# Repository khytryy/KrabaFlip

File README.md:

# KrabaFlip

## My DIY console based on RPI CM5

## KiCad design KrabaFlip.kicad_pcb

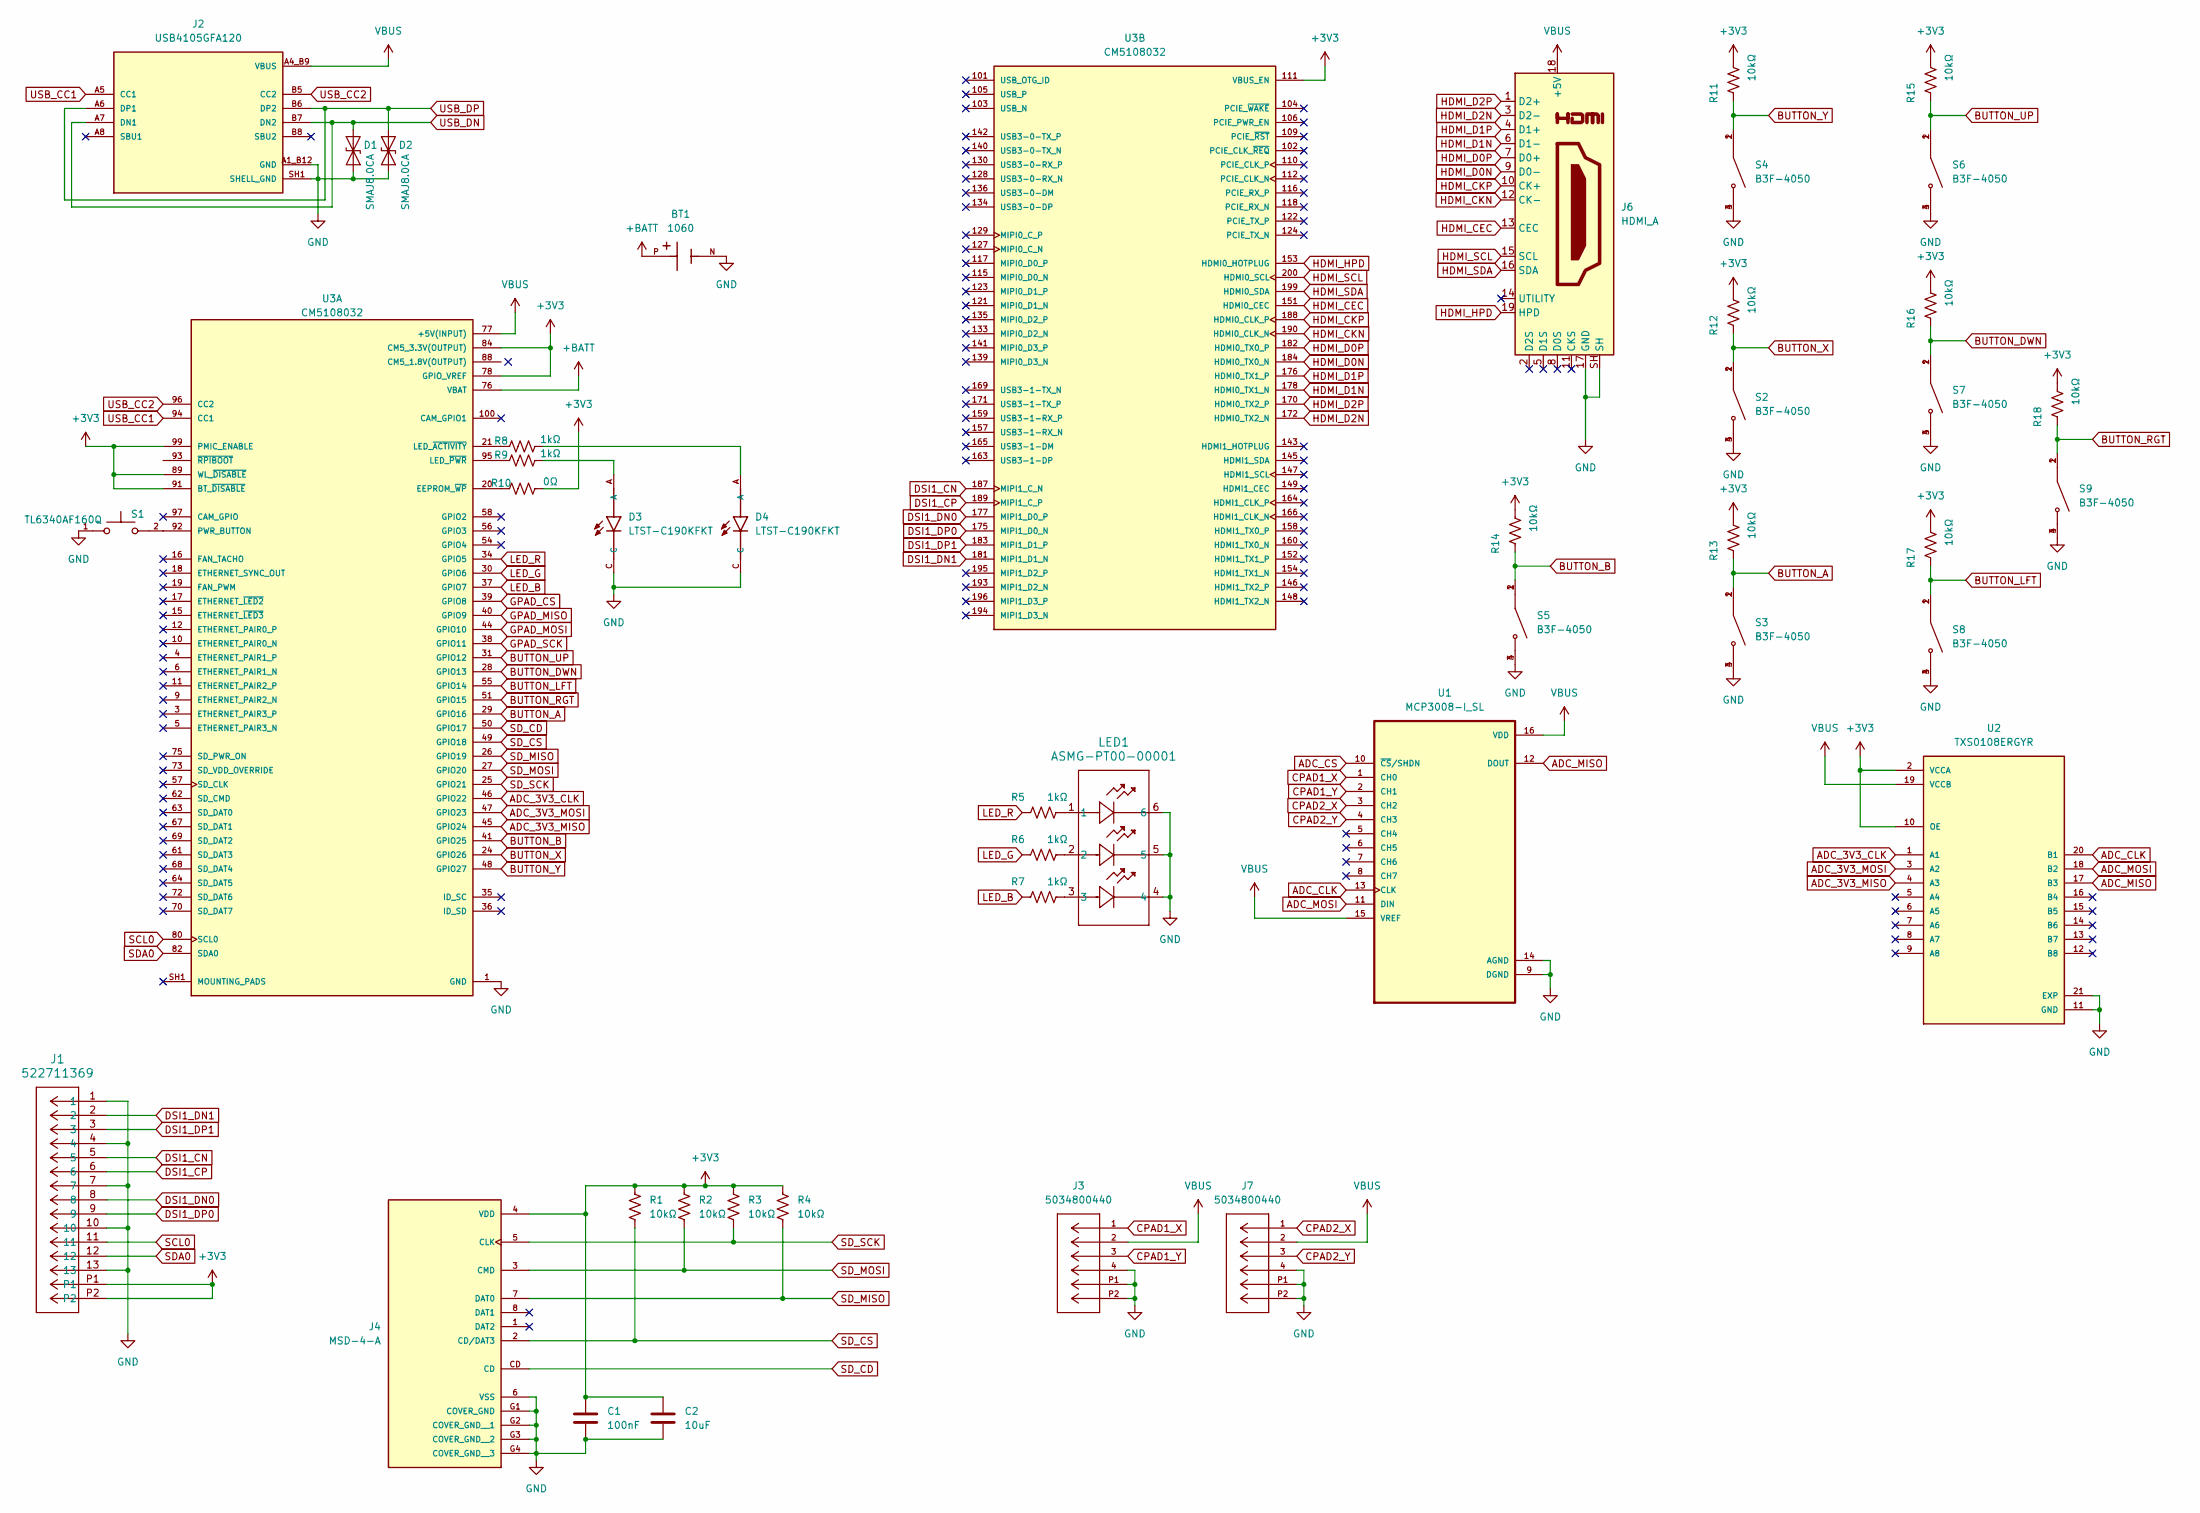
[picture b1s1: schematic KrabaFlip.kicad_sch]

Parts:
BT1: 1060; BAT_1060; PARTREV L; DigiKey_Part_Number 36-1060-ND
C1: 100nF; C_0402_1005Metric
C2: 10uF; C_0402_1005Metric
D1, D2: SMAJ8.0CA; D_SMA
D3, D4: LTST-C190KFKT; LEDM1608X80; DigiKey_Part_Number 160-1434-1-ND
J1: 522711369; CON_522711369_MOL
J2: USB4105GFA120; GCT_USB4105GFA120; PARTREV B3; DigiKey_Part_Number 2073-USB4105-GF-A-120CT-ND
J3, J7: 5034800440; CON_5034800440_MOL; MANUFACTURER_PART_NUMBER 5034800440; DigiKey_Part_Number 900-5034800440CT-ND
J4: MSD-4-A; CUI_MSD-4-A; PARTREV 1.0
J6: HDMI_A; HDMI_A_Amphenol_10029449-x01xLF_Horizontal
LED1: ASMG-PT00-00001; ASMG-PT00_BRA
R1, R2, R3, R4, R11, R12, R13, R14, R15, R16, R17, R18: 10kΩ; R_0402_1005Metric
R5, R6, R7, R8, R9: 1kΩ; R_0402_1005Metric
R10: 0Ω; R_0402_1005Metric
S1: TL6340AF160Q; SW_TL6340AF160Q; PARTREV 10.23.2019; DigiKey_Part_Number 141-TL6340AF160QCT-ND
S2, S3, S4, S5, S6, S7, S8, S9: B3F-4050; SW_B3F-4050; Digi-Key_Part_Number SW414-ND
U1: MCP3008-I_SL; SOIC127P600X175-16N; DigiKey_Part_Number MCP3008-I/SL-ND
U2: TXS0108ERGYR; IC_TXS0108ERGYR; PARTREV H; DigiKey_Part_Number 296-24806-1-ND
U3: CM5108032; MODULE_CM5108032; PARTREV 2024-11-27

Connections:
+3V3: C1.1, C2.1, J1.P1, J1.P2, J4.4 (VDD), R1.1, R2.1, R3.1, R4.1, R10.2, R11.2, R12.2, R13.2, R14.2, R15.2, R16.2, R17.2, R18.2, U2.2 (VCCA), U2.10 (OE), U3.78 (GPIO_VREF), U3.84 (CM5_3.3V(OUTPUT)), U3.86 (CM5_3.3V(OUTPUT)), U3.89 (WL_~DISABLE), U3.91 (BT_~DISABLE), U3.99 (PMIC_ENABLE), U3.111 (VBUS_EN)
+BATT: BT1.P, U3.76 (VBAT)
ADC_3V3_CLK: U2.1 (A1), U3.46 (GPIO22)
ADC_3V3_MISO: U2.4 (A3), U3.45 (GPIO24)
ADC_3V3_MOSI: U2.3 (A2), U3.47 (GPIO23)
ADC_CLK: U1.13 (CLK), U2.20 (B1)
ADC_CS: U1.10 (~CS/SHDN)
ADC_MISO: U1.12 (DOUT), U2.17 (B3)
ADC_MOSI: U1.11 (DIN), U2.18 (B2)
BUTTON_A: R13.1, S3.1, S3.2, U3.29 (GPIO16)
BUTTON_B: R14.1, S5.1, S5.2, U3.41 (GPIO25)
BUTTON_DWN: R16.1, S7.1, S7.2, U3.28 (GPIO13)
BUTTON_LFT: R17.1, S8.1, S8.2, U3.55 (GPIO14)
BUTTON_RGT: R18.1, S9.1, S9.2, U3.51 (GPIO15)
BUTTON_UP: R15.1, S6.1, S6.2, U3.31 (GPIO12)
BUTTON_X: R12.1, S2.1, S2.2, U3.24 (GPIO26)
BUTTON_Y: R11.1, S4.1, S4.2, U3.48 (GPIO27)
CM5_1.8V(OUTPUT): U3.88 (CM5_1.8V(OUTPUT)), U3.90 (CM5_1.8V(OUTPUT))
CPAD1_X: J3.1, U1.1 (CH0)
CPAD1_Y: J3.3, U1.2 (CH1)
CPAD2_X: J7.1, U1.3 (CH2)
CPAD2_Y: J7.3, U1.4 (CH3)
DSI1_CN: J1.5, U3.187 (MIPI1_C_N)
DSI1_CP: J1.6, U3.189 (MIPI1_C_P)
DSI1_DN0: J1.8, U3.177 (MIPI1_D0_P)
DSI1_DN1: J1.2, U3.181 (MIPI1_D1_N)
DSI1_DP0: J1.9, U3.175 (MIPI1_D0_N)
DSI1_DP1: J1.3, U3.183 (MIPI1_D1_P)
GND: BT1.N, C1.2, C2.2, D1.1 (A1), D2.1 (A1), D3.C, D4.C, J1.1, J1.4, J1.7, J1.10, J1.13, J2.A1_B12 (GND), J2.B1_A12 (GND), J2.SH1 (SHELL_GND), J2.SH2 (SHELL_GND), J2.SH3 (SHELL_GND), J2.SH4 (SHELL_GND), J3.4, J3.P1, J3.P2, J4.6 (VSS), J4.G1 (COVER_GND), J4.G2 (COVER_GND__1), J4.G3 (COVER_GND__2), J4.G4 (COVER_GND__3), J6.17 (GND), J6.SH, J7.4, J7.P1, J7.P2, LED1.4, LED1.5, LED1.6, S1.1, S2.3, S2.4, S3.3, S3.4, S4.3, S4.4, S5.3, S5.4, S6.3, S6.4, S7.3, S7.4, S8.3, S8.4, S9.3, S9.4, U1.9 (DGND), U1.14 (AGND), U2.11 (GND), U2.21 (EXP), U3.1 (GND), U3.2 (GND), U3.7 (GND), U3.8 (GND), U3.13 (GND), U3.14 (GND), U3.22 (GND), U3.23 (GND), U3.32 (GND), U3.33 (GND), U3.42 (GND), U3.43 (GND), U3.52 (GND), U3.53 (GND), U3.59 (GND), U3.60 (GND), U3.65 (GND), U3.66 (GND), U3.71 (GND), U3.74 (GND), U3.98 (GND), U3.107 (GND), U3.108 (GND), U3.113 (GND), U3.114 (GND), U3.119 (GND), U3.120 (GND), U3.125 (GND), U3.126 (GND), U3.131 (GND), U3.132 (GND), U3.137 (GND), U3.138 (GND), U3.144 (GND), U3.150 (GND), U3.155 (GND), U3.156 (GND), U3.161 (GND), U3.162 (GND), U3.167 (GND), U3.168 (GND), U3.173 (GND), U3.174 (GND), U3.179 (GND), U3.180 (GND), U3.185 (GND), U3.186 (GND), U3.191 (GND), U3.192 (GND), U3.197 (GND), U3.198 (GND)
GPAD_CS: U3.39 (GPIO8)
GPAD_MISO: U3.40 (GPIO9)
GPAD_MOSI: U3.44 (GPIO10)
GPAD_SCK: U3.38 (GPIO11)
HDMI_CEC: J6.13 (CEC), U3.151 (HDMI0_CEC)
HDMI_CKN: J6.12 (CK-), U3.190 (HDMI0_CLK_N)
HDMI_CKP: J6.10 (CK+), U3.188 (HDMI0_CLK_P)
HDMI_D0N: J6.9 (D0-), U3.184 (HDMI0_TX0_N)
HDMI_D0P: J6.7 (D0+), U3.182 (HDMI0_TX0_P)
HDMI_D1N: J6.6 (D1-), U3.178 (HDMI0_TX1_N)
HDMI_D1P: J6.4 (D1+), U3.176 (HDMI0_TX1_P)
HDMI_D2N: J6.3 (D2-), U3.172 (HDMI0_TX2_N)
HDMI_D2P: J6.1 (D2+), U3.170 (HDMI0_TX2_P)
HDMI_HPD: J6.19 (HPD), U3.153 (HDMI0_HOTPLUG)
HDMI_SCL: J6.15 (SCL), U3.200 (HDMI0_SCL)
HDMI_SDA: J6.16 (SDA), U3.199 (HDMI0_SDA)
LED_B: R7.1, U3.37 (GPIO7)
LED_G: R6.1, U3.30 (GPIO6)
LED_R: R5.1, U3.34 (GPIO5)
unnamed: D3.A, R9.2
unnamed: D4.A, R8.2
unnamed: LED1.1, R5.2
unnamed: LED1.2, R6.2
unnamed: LED1.3, R7.2
unnamed: R10.1, U3.20 (EEPROM_~WP)
unnamed: R8.1, U3.21 (LED_~ACTIVITY)
unnamed: R9.1, U3.95 (LED_~PWR)
unnamed: S1.2, U3.92 (PWR_BUTTON)
SCL0: J1.11, U3.80 (SCL0)
SDA0: J1.12, U3.82 (SDA0)
SD_CD: J4.CD, U3.50 (GPIO17)
SD_CS: J4.2 (CD/DAT3), R1.2, U3.49 (GPIO18)
SD_MISO: J4.7 (DAT0), R4.2, U3.26 (GPIO19)
SD_MOSI: J4.3 (CMD), R2.2, U3.27 (GPIO20)
SD_SCK: J4.5 (CLK), R3.2, U3.25 (GPIO21)
USB_CC1: J2.A5 (CC1), U3.94 (CC1)
USB_CC2: J2.B5 (CC2), U3.96 (CC2)
USB_DN: D1.2 (A2), J2.A7 (DN1), J2.B7 (DN2)
USB_DP: D2.2 (A2), J2.A6 (DP1), J2.B6 (DP2)
VBUS: J2.A4_B9 (VBUS), J2.B4_A9 (VBUS), J3.2, J6.18 (+5V), J7.2, U1.15 (VREF), U1.16 (VDD), U2.19 (VCCB), U3.77 (+5V(INPUT)), U3.79 (+5V(INPUT)), U3.81 (+5V(INPUT)), U3.83 (+5V(INPUT)), U3.85 (+5V(INPUT)), U3.87 (+5V(INPUT))

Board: 2 copper layers, 44 parts (5 on the bottom side), 64 nets, no tracks yet.

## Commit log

2025-11-29 Add DSI, JST-PH connectors
2025-11-30 Add joystick connectors
2025-12-01 Add KrabaFlip.kicad_pcb
2025-12-02 Remove messed up tracks
